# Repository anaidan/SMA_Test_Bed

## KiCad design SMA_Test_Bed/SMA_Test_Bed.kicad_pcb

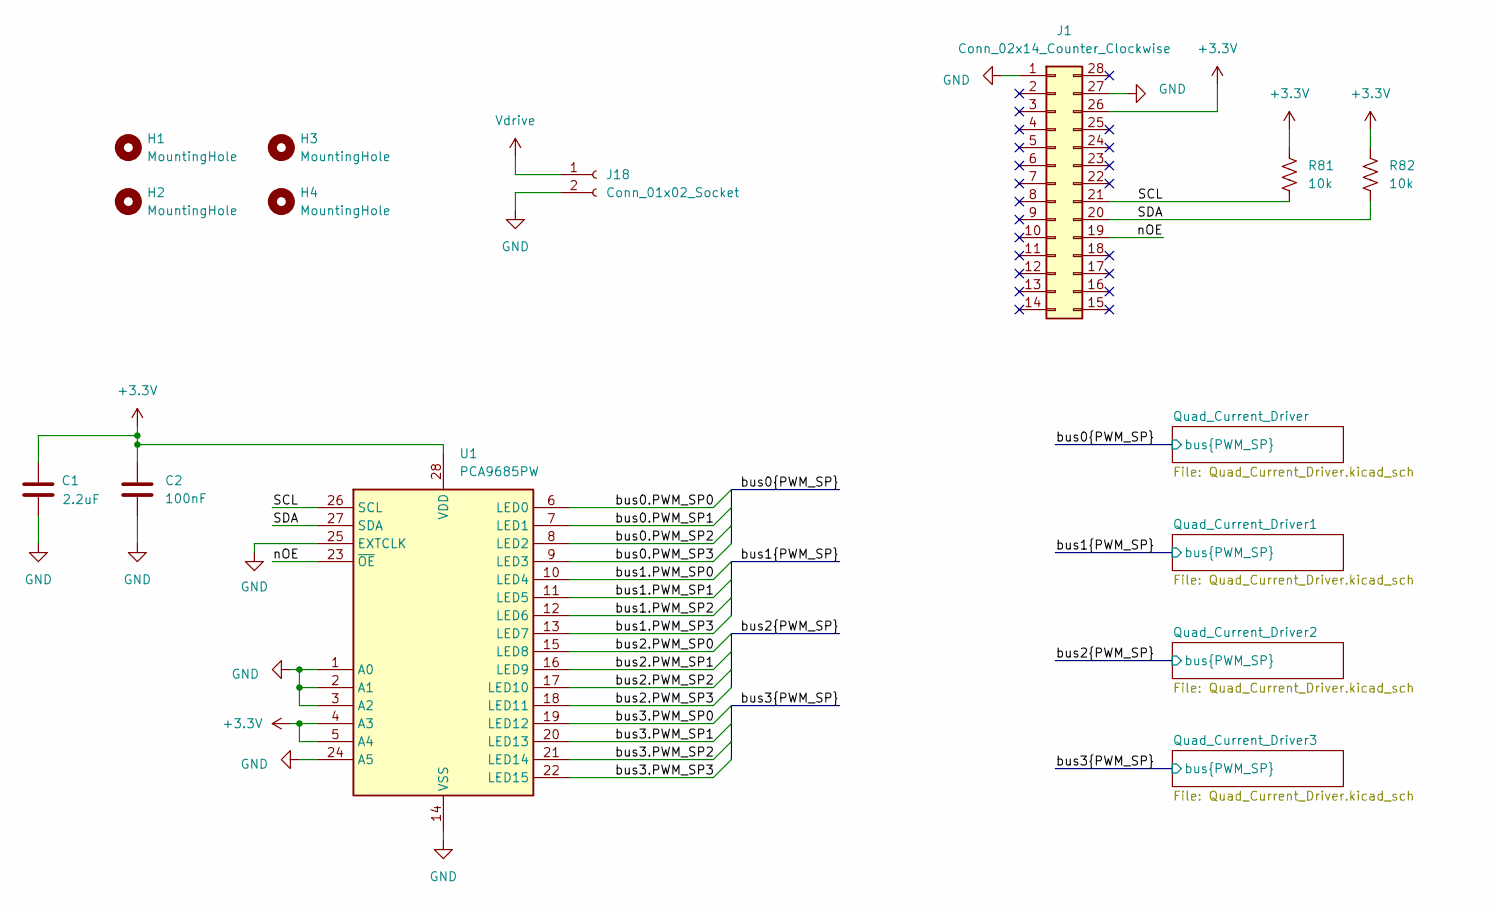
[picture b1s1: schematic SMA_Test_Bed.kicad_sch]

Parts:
C1: 2.2uF; C_0805_2012Metric; Digikey PN 490-14467-1-ND
C2: 100nF; C_0603_1608Metric; Digikey PN 311-1088-1-ND
H1, H2, H3, H4: MountingHole; MountingHole_2.7mm_Pad_Via
J1: Conn_02x14_Counter_Clockwise; Teensy_4_0; Digikey PN SSW-114-01-G-S-LL-ND
J18: Conn_01x02_Socket; SMA_MHs
R81, R82: 10k; R_0603_1608Metric; Digikey PN 311-10.0KHRCT-ND
U1: PCA9685PW; TSSOP-28_4.4x9.7mm_P0.65mm; Digikey PN 568-5931-1-ND

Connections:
+3.3V: C1.1, C2.1, J1.26, R81.1, R82.2, U1.4 (A3), U1.5 (A4), U1.28 (VDD); also elsewhere on the board
/SCL: J1.21, R81.2, U1.26 (SCL)
/SDA: J1.20, R82.1, U1.27 (SDA)
/bus0.PWM_SP0: U1.6 (LED0); also elsewhere on the board
/bus0.PWM_SP1: U1.7 (LED1); also elsewhere on the board
/bus0.PWM_SP2: U1.8 (LED2); also elsewhere on the board
/bus0.PWM_SP3: U1.9 (LED3); also elsewhere on the board
/bus1.PWM_SP0: U1.10 (LED4); also elsewhere on the board
/bus1.PWM_SP1: U1.11 (LED5); also elsewhere on the board
/bus1.PWM_SP2: U1.12 (LED6); also elsewhere on the board
/bus1.PWM_SP3: U1.13 (LED7); also elsewhere on the board
/bus2.PWM_SP0: U1.15 (LED8); also elsewhere on the board
/bus2.PWM_SP1: U1.16 (LED9); also elsewhere on the board
/bus2.PWM_SP2: U1.17 (LED10); also elsewhere on the board
/bus2.PWM_SP3: U1.18 (LED11); also elsewhere on the board
/bus3.PWM_SP0: U1.19 (LED12); also elsewhere on the board
/bus3.PWM_SP1: U1.20 (LED13); also elsewhere on the board
/bus3.PWM_SP2: U1.21 (LED14); also elsewhere on the board
/bus3.PWM_SP3: U1.22 (LED15); also elsewhere on the board
/nOE: J1.19, U1.23 (~OE)
GND: C1.2, C2.2, J1.1, J1.27, J18.2, U1.1 (A0), U1.2 (A1), U1.3 (A2), U1.14 (VSS), U1.24 (A5), U1.25 (EXTCLK); also elsewhere on the board
Vdrive: J18.1; also elsewhere on the board

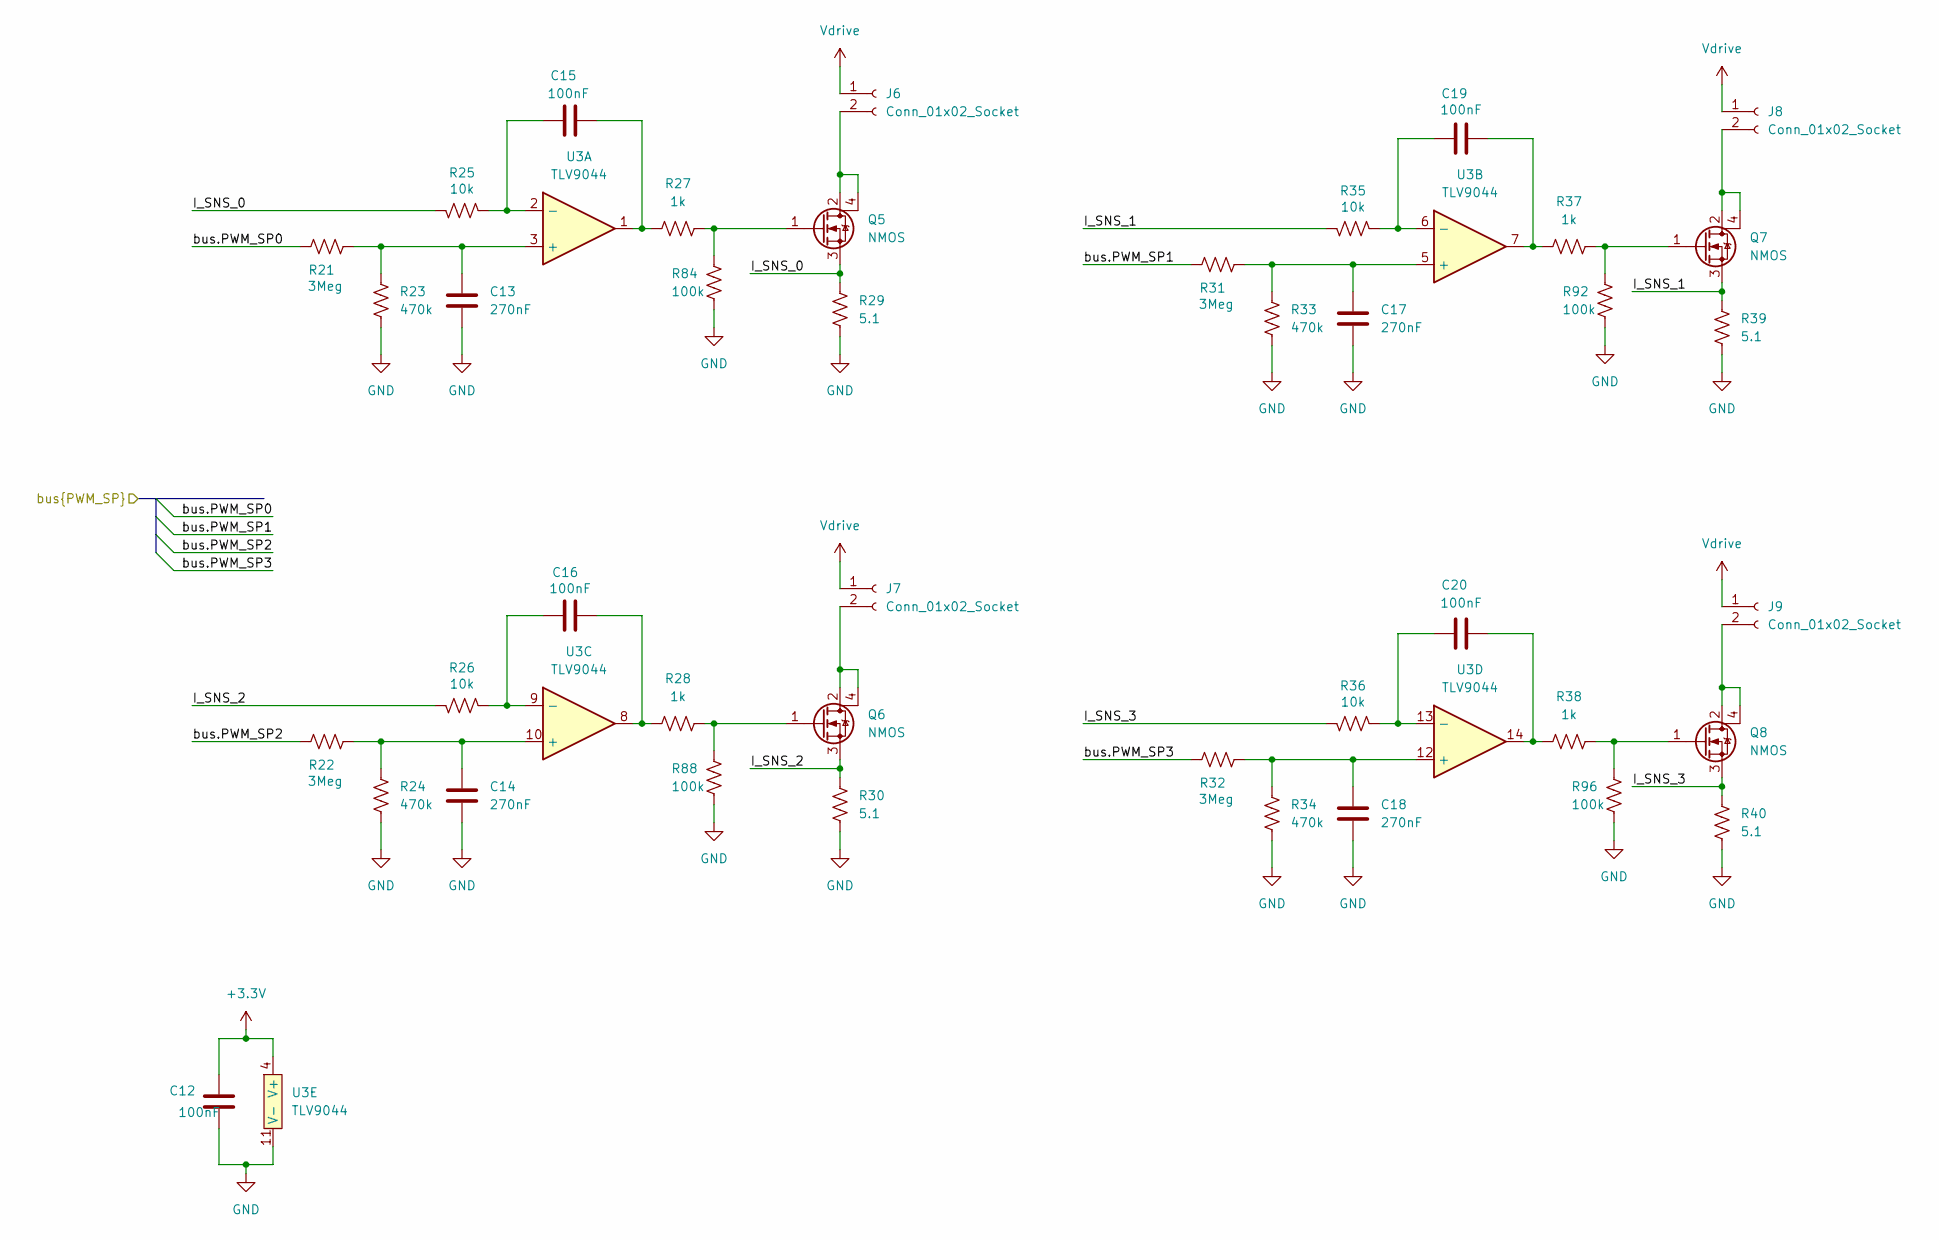
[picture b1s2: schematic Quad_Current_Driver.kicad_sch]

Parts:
C12, C15, C16, C19, C20: 100nF; C_0603_1608Metric; Digikey PN 311-1088-1-ND
C13, C14, C17, C18: 270nF; C_0603_1608Metric; Digikey PN 490-16405-1-ND
J6, J7, J8, J9: Conn_01x02_Socket; SMA_MHs_Small
Q5, Q6, Q7, Q8: NMOS; SOT-223; Digikey PN DMN3032LE-13DICT-ND
R21, R22, R31, R32: 3Meg; R_0603_1608Metric; Digikey PN RMCF0603FT3M00CT-ND
R23, R24, R33, R34: 470k; R_0603_1608Metric; Digikey PN YAG4560CT-ND
R25, R26, R35, R36: 10k; R_0603_1608Metric; Digikey PN 311-10.0KHRCT-ND
R27, R28, R37, R38: 1k; R_0603_1608Metric; Digikey PN 311-1.00KHRCT-ND
R29, R30, R39, R40: 5.1; R_0603_1608Metric; Digikey PN A103115CT-ND
R84, R88, R92, R96: 100k; R_0603_1608Metric; Digikey PN P100KHCT-ND
U3: TLV9044; SOIC-14_3.9x8.7mm_P1.27mm; Digikey PN 296-TLV9044IDRCT-ND

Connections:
+3.3V: C12.1, U3.4 (V+); also elsewhere on the board
/Quad_Current_Driver1/I_SNS_0: Q5.3 (S), R25.1, R29.2
/Quad_Current_Driver1/I_SNS_1: Q7.3 (S), R35.1, R39.2
/Quad_Current_Driver1/I_SNS_2: Q6.3 (S), R26.1, R30.2
/Quad_Current_Driver1/I_SNS_3: Q8.3 (S), R36.1, R40.2
/bus1.PWM_SP0: R21.2; also elsewhere on the board
/bus1.PWM_SP1: R31.2; also elsewhere on the board
/bus1.PWM_SP2: R22.2; also elsewhere on the board
/bus1.PWM_SP3: R32.2; also elsewhere on the board
GND: C12.2, C13.2, C14.2, C17.2, C18.2, R23.2, R24.2, R29.1, R30.1, R33.2, R34.2, R39.1, R40.1, R84.1, R88.1, R92.1, R96.1, U3.11 (V-); also elsewhere on the board
unnamed: C15.2, R27.1, U3.1
unnamed: C16.2, R28.1, U3.8
unnamed: C19.2, R37.1, U3.7
unnamed: C20.2, R38.1, U3.14
unnamed: J6.2, Q5.2 (D), Q5.4 (D)
unnamed: J7.2, Q6.2 (D), Q6.4 (D)
unnamed: J8.2, Q7.2 (D), Q7.4 (D)
unnamed: J9.2, Q8.2 (D), Q8.4 (D)
unnamed: Q5.1 (G), R27.2, R84.2
unnamed: Q6.1 (G), R28.2, R88.2
unnamed: Q7.1 (G), R37.2, R92.2
unnamed: Q8.1 (G), R38.2, R96.2
unnamed: C13.1, R21.1, R23.1, U3.3 (+)
unnamed: C15.1, R25.2, U3.2 (-)
unnamed: C17.1, R31.1, R33.1, U3.5 (+)
unnamed: C19.1, R35.2, U3.6 (-)
unnamed: C14.1, R22.1, R24.1, U3.10 (+)
unnamed: C16.1, R26.2, U3.9 (-)
unnamed: C18.1, R32.1, R34.1, U3.12 (+)
unnamed: C20.1, R36.2, U3.13 (-)
Vdrive: J6.1, J7.1, J8.1, J9.1; also elsewhere on the board

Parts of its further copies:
C3, C6, C7, C10, C11, C21, C24, C25, C28, C29, C30, C33, C34, C37, C38: 100nF; C_0603_1608Metric; Digikey PN 311-1088-1-ND
C4, C5, C8, C9, C22, C23, C26, C27, C31, C32, C35, C36: 270nF; C_0603_1608Metric; Digikey PN 490-16405-1-ND
J2, J3, J4, J5, J10, J11, J12, J13, J14, J15, J16, J17: Conn_01x02_Socket; SMA_MHs_Small
Q1, Q2, Q3, Q4, Q9, Q10, Q11, Q12, Q13, Q14, Q15, Q16: NMOS; SOT-223; Digikey PN DMN3032LE-13DICT-ND
R1, R2, R11, R12, R41, R42, R51, R52, R61, R62, R71, R72: 3Meg; R_0603_1608Metric; Digikey PN RMCF0603FT3M00CT-ND
R3, R4, R13, R14, R43, R44, R53, R54, R63, R64, R73, R74: 470k; R_0603_1608Metric; Digikey PN YAG4560CT-ND
R5, R6, R15, R16, R45, R46, R55, R56, R65, R66, R75, R76: 10k; R_0603_1608Metric; Digikey PN 311-10.0KHRCT-ND
R7, R8, R17, R18, R47, R48, R57, R58, R67, R68, R77, R78: 1k; R_0603_1608Metric; Digikey PN 311-1.00KHRCT-ND
R83, R85, R86, R87, R89, R90, R91, R93, R94, R95, R97, R98: 100k; R_0603_1608Metric; Digikey PN P100KHCT-ND
U2, U4, U5: TLV9044; SOIC-14_3.9x8.7mm_P1.27mm; Digikey PN 296-TLV9044IDRCT-ND

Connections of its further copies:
+3.3V: C3.1, C21.1, C30.1, U2.4 (V+), U4.4 (V+), U5.4 (V+); also elsewhere on the board
/Quad_Current_Driver2/I_SNS_0: Q9.3 (S), R45.1; also elsewhere on the board
/Quad_Current_Driver2/I_SNS_1: Q11.3 (S), R55.1; also elsewhere on the board
/Quad_Current_Driver2/I_SNS_2: Q10.3 (S), R46.1; also elsewhere on the board
/Quad_Current_Driver2/I_SNS_3: Q12.3 (S), R56.1; also elsewhere on the board
/Quad_Current_Driver3/I_SNS_0: Q13.3 (S), R65.1; also elsewhere on the board
/Quad_Current_Driver3/I_SNS_1: Q15.3 (S), R75.1; also elsewhere on the board
/Quad_Current_Driver3/I_SNS_2: Q14.3 (S), R66.1; also elsewhere on the board
/Quad_Current_Driver3/I_SNS_3: Q16.3 (S), R76.1; also elsewhere on the board
/Quad_Current_Driver/I_SNS_0: Q1.3 (S), R5.1; also elsewhere on the board
/Quad_Current_Driver/I_SNS_1: Q3.3 (S), R15.1; also elsewhere on the board
/Quad_Current_Driver/I_SNS_2: Q2.3 (S), R6.1; also elsewhere on the board
/Quad_Current_Driver/I_SNS_3: Q4.3 (S), R16.1; also elsewhere on the board
/bus0.PWM_SP0: R1.2; also elsewhere on the board
/bus0.PWM_SP1: R11.2; also elsewhere on the board
/bus0.PWM_SP2: R2.2; also elsewhere on the board
/bus0.PWM_SP3: R12.2; also elsewhere on the board
/bus2.PWM_SP0: R41.2; also elsewhere on the board
/bus2.PWM_SP1: R51.2; also elsewhere on the board
/bus2.PWM_SP2: R42.2; also elsewhere on the board
/bus2.PWM_SP3: R52.2; also elsewhere on the board
/bus3.PWM_SP0: R61.2; also elsewhere on the board
/bus3.PWM_SP1: R71.2; also elsewhere on the board
/bus3.PWM_SP2: R62.2; also elsewhere on the board
/bus3.PWM_SP3: R72.2; also elsewhere on the board
GND: C3.2, C4.2, C5.2, C8.2, C9.2, C21.2, C22.2, C23.2, C26.2, C27.2, C30.2, C31.2, C32.2, C35.2, C36.2, R3.2, R4.2, R13.2, R14.2, R43.2, R44.2, R53.2, R54.2, R63.2, R64.2, R73.2, R74.2, R83.1, R85.1, R86.1, R87.1, R89.1, R90.1, R91.1, R93.1, R94.1, R95.1, R97.1, R98.1, U2.11 (V-), U4.11 (V-), U5.11 (V-); also elsewhere on the board
unnamed: C6.2, R7.1, U2.1
unnamed: C7.2, R8.1, U2.8
unnamed: C10.2, R17.1, U2.7
unnamed: C11.2, R18.1, U2.14
unnamed: C24.2, R47.1, U4.1
unnamed: C25.2, R48.1, U4.8
unnamed: C28.2, R57.1, U4.7
unnamed: C29.2, R58.1, U4.14
unnamed: C33.2, R67.1, U5.1
unnamed: C34.2, R68.1, U5.8
unnamed: C37.2, R77.1, U5.7
unnamed: C38.2, R78.1, U5.14
unnamed: J2.2, Q1.2 (D), Q1.4 (D)
unnamed: J3.2, Q2.2 (D), Q2.4 (D)
unnamed: J4.2, Q3.2 (D), Q3.4 (D)
unnamed: J5.2, Q4.2 (D), Q4.4 (D)
unnamed: J10.2, Q9.2 (D), Q9.4 (D)
unnamed: J11.2, Q10.2 (D), Q10.4 (D)
unnamed: J12.2, Q11.2 (D), Q11.4 (D)
unnamed: J13.2, Q12.2 (D), Q12.4 (D)
unnamed: J14.2, Q13.2 (D), Q13.4 (D)
unnamed: J15.2, Q14.2 (D), Q14.4 (D)
unnamed: J16.2, Q15.2 (D), Q15.4 (D)
unnamed: J17.2, Q16.2 (D), Q16.4 (D)
unnamed: Q1.1 (G), R7.2, R83.2
unnamed: Q2.1 (G), R8.2, R87.2
unnamed: Q3.1 (G), R17.2, R91.2
unnamed: Q4.1 (G), R18.2, R95.2
unnamed: Q9.1 (G), R47.2, R85.2
unnamed: Q10.1 (G), R48.2, R89.2
unnamed: Q11.1 (G), R57.2, R93.2
unnamed: Q12.1 (G), R58.2, R97.2
unnamed: Q13.1 (G), R67.2, R86.2
unnamed: Q14.1 (G), R68.2, R90.2
unnamed: Q15.1 (G), R77.2, R94.2
unnamed: Q16.1 (G), R78.2, R98.2
unnamed: C4.1, R1.1, R3.1, U2.3 (+)
unnamed: C6.1, R5.2, U2.2 (-)
unnamed: C8.1, R11.1, R13.1, U2.5 (+)
unnamed: C10.1, R15.2, U2.6 (-)
unnamed: C5.1, R2.1, R4.1, U2.10 (+)
unnamed: C7.1, R6.2, U2.9 (-)
unnamed: C9.1, R12.1, R14.1, U2.12 (+)
unnamed: C11.1, R16.2, U2.13 (-)
unnamed: C22.1, R41.1, R43.1, U4.3 (+)
unnamed: C24.1, R45.2, U4.2 (-)
unnamed: C26.1, R51.1, R53.1, U4.5 (+)
unnamed: C28.1, R55.2, U4.6 (-)
unnamed: C23.1, R42.1, R44.1, U4.10 (+)
unnamed: C25.1, R46.2, U4.9 (-)
unnamed: C27.1, R52.1, R54.1, U4.12 (+)
unnamed: C29.1, R56.2, U4.13 (-)
unnamed: C31.1, R61.1, R63.1, U5.3 (+)
unnamed: C33.1, R65.2, U5.2 (-)
unnamed: C35.1, R71.1, R73.1, U5.5 (+)
unnamed: C37.1, R75.2, U5.6 (-)
unnamed: C32.1, R62.1, R64.1, U5.10 (+)
unnamed: C34.1, R66.2, U5.9 (-)
unnamed: C36.1, R72.1, R74.1, U5.12 (+)
unnamed: C38.1, R76.2, U5.13 (-)
Vdrive: J2.1, J3.1, J4.1, J5.1, J10.1, J11.1, J12.1, J13.1, J14.1, J15.1, J16.1, J17.1; also elsewhere on the board

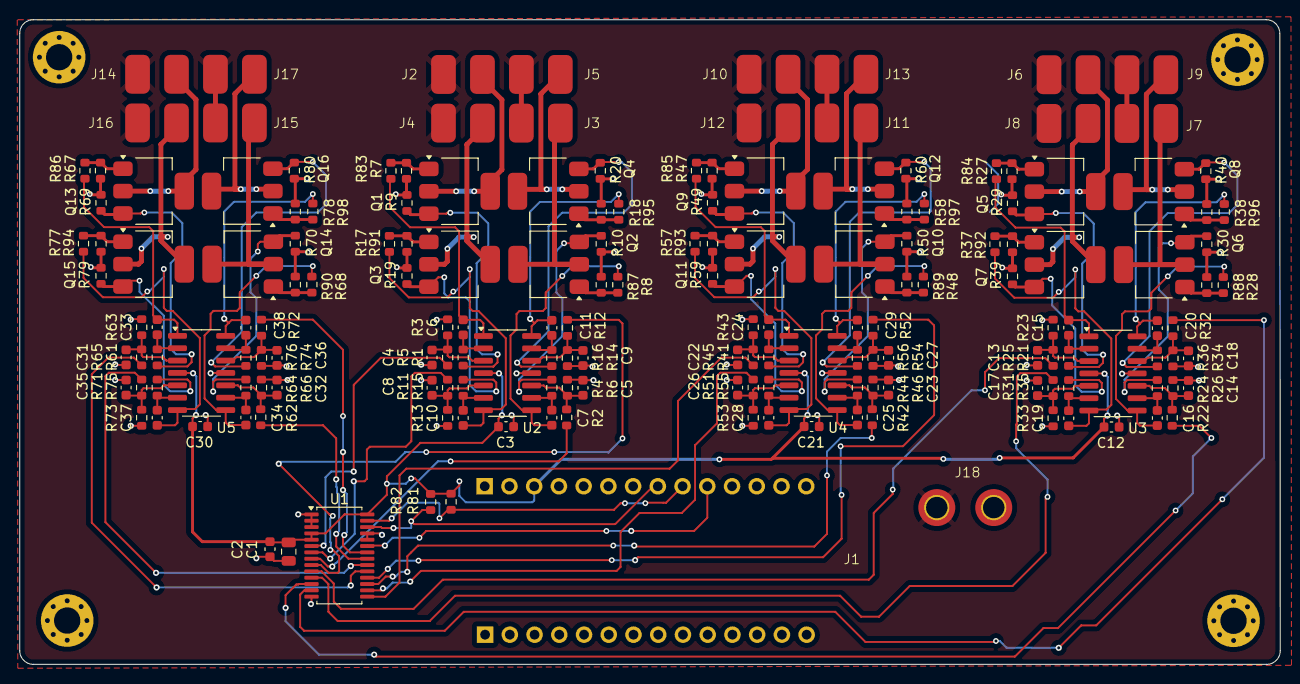
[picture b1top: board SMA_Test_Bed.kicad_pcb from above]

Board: 2 copper layers, 129.4 x 66.2 mm, 179 parts (0 on the bottom side), 118 nets.

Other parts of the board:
R9, R10, R19, R20, R49, R50, R59, R60, R69, R70, R79, R80: 5; R_0603_1608Metric

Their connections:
/Quad_Current_Driver2/I_SNS_0: R49.2; also elsewhere on the board
/Quad_Current_Driver2/I_SNS_1: R59.2; also elsewhere on the board
/Quad_Current_Driver2/I_SNS_2: R50.2; also elsewhere on the board
/Quad_Current_Driver2/I_SNS_3: R60.2; also elsewhere on the board
/Quad_Current_Driver3/I_SNS_0: R69.2; also elsewhere on the board
/Quad_Current_Driver3/I_SNS_1: R79.2; also elsewhere on the board
/Quad_Current_Driver3/I_SNS_2: R70.2; also elsewhere on the board
/Quad_Current_Driver3/I_SNS_3: R80.2; also elsewhere on the board
/Quad_Current_Driver/I_SNS_0: R9.2; also elsewhere on the board
/Quad_Current_Driver/I_SNS_1: R19.2; also elsewhere on the board
/Quad_Current_Driver/I_SNS_2: R10.2; also elsewhere on the board
/Quad_Current_Driver/I_SNS_3: R20.2; also elsewhere on the board
GND: R9.1, R10.1, R19.1, R20.1, R49.1, R50.1, R59.1, R60.1, R69.1, R70.1, R79.1, R80.1; also elsewhere on the board

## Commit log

2024-08-19 Layout draft complete
2024-08-21 Added passive values
2024-08-22 Time of fabrication
